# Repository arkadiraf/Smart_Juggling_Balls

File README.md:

# Smart Juggling Balls
Smart Juggling Balls is a project of mine which consists of 3 basic modules: 
arduino pro mini (compatible) MPU 6050 and nrf24
and a bunch of LEDS of course :)
The files I publish include the PCB manufacturing Gerber files
STL files for the casing (ment for 3d printing)
and some code I wrote.
The idea is to have colorful and happy juggling balls which can change lightning based on the sensor readings 
and remote maniputations communicating via nrf24.

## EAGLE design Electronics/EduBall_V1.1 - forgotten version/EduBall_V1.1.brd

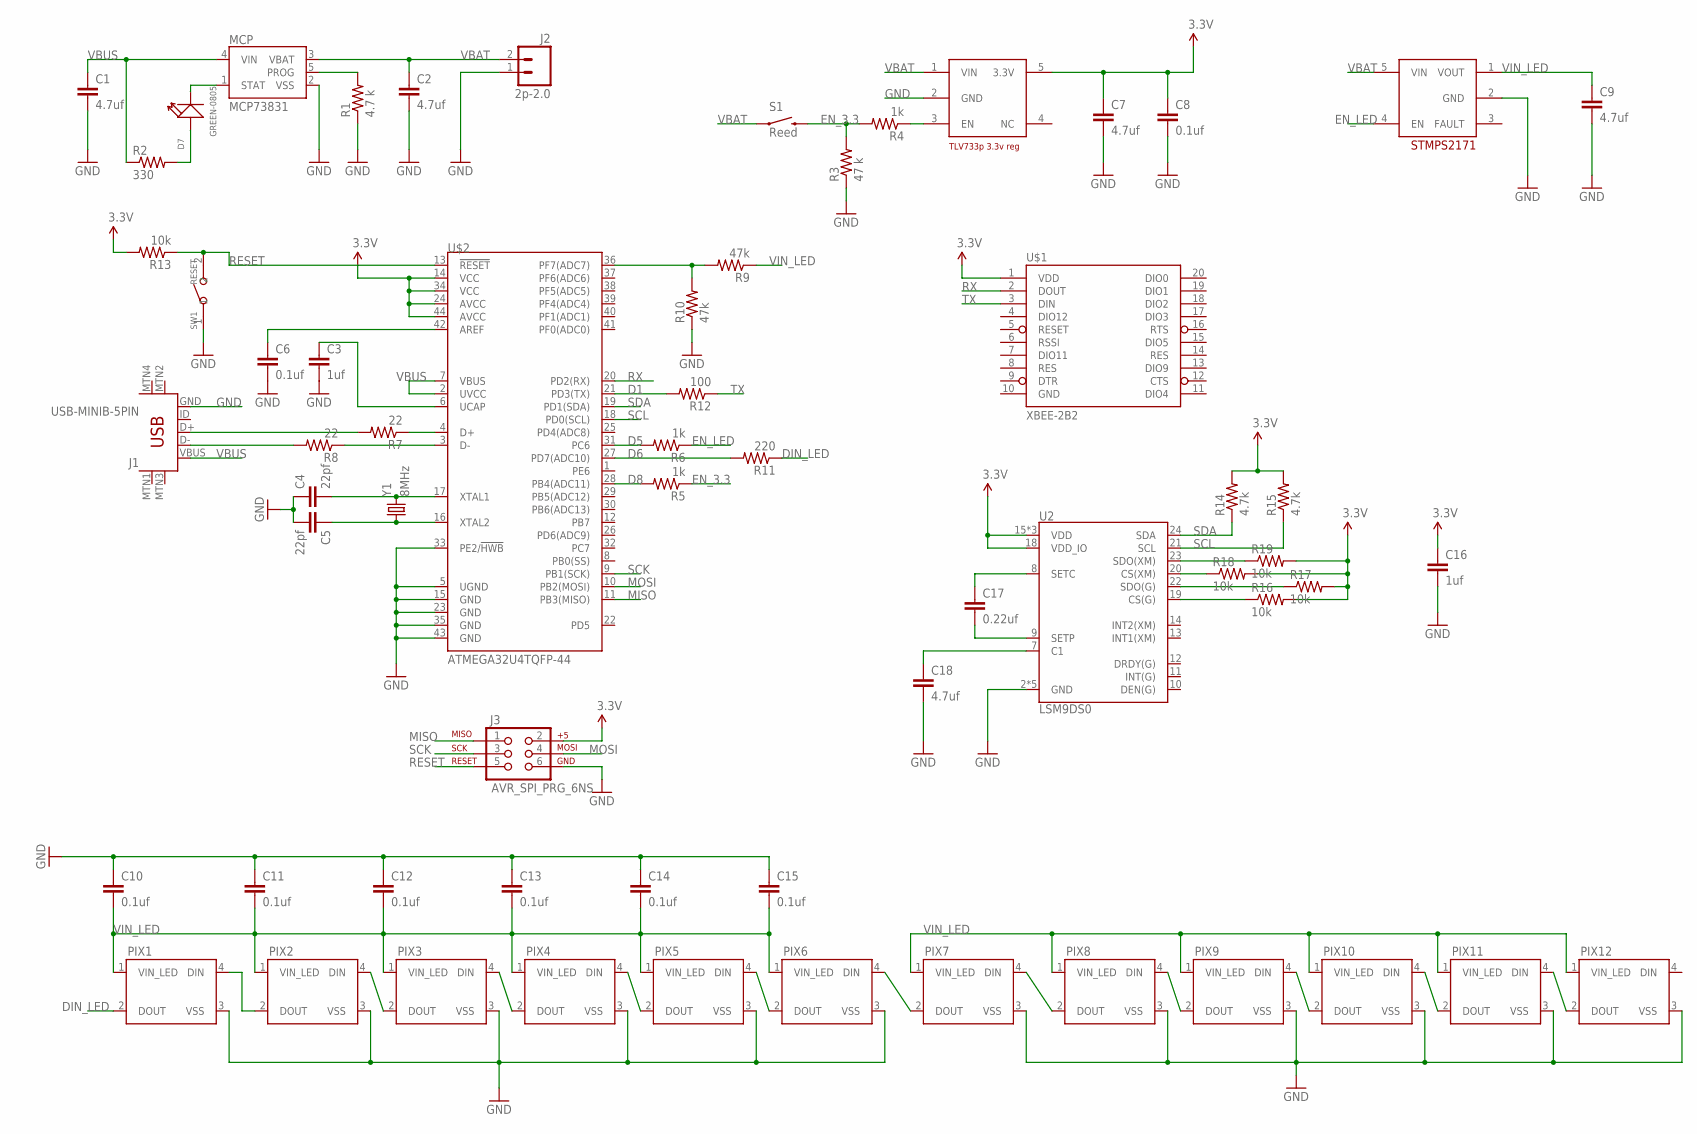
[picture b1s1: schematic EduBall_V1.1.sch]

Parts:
C1, C2, C7, C9, C18: 4.7uf; 0805
C3, C16: 1uf; 0805
C4, C5: 22pf; 0805
C6, C8, C10, C11, C12, C13, C14, C15: 0.1uf; 0805
C17: 0.22uf; 0805
D7: GREEN-0805; LED-0805
J1: USB-MINIB-5PIN; USB-MINIB
J2: 2p-2.0; JST-2-PTH-VERT
J3: AVR_SPI_PRG_6NS; 2X3-NS
MCP: MCP73831; SOT23-5
PIX1, PIX2, PIX3, PIX4, PIX5, PIX6, PIX7, PIX8, PIX9, PIX10, PIX11, PIX12: WS2812B
R1: 4.7 k; 0805
R2: 330; 0805
R3: 47 k; 0805
R4, R5, R6: 1k; 0805
R7, R8: 22; 0805
R9, R10: 47k; 0805
R11: 220; 0805
R12: 100; 0805
R13, R16, R17, R18, R19: 10k; 0805
R14, R15: 4.7k; 0805
S1: Reed; REED_SWITCH_PTH
STMP: STMPS2171; SOT23-5
SW1: RESET; SW2-2.6-3.0X2.5X1.2+0.4MM
TLV: TLV3333P; SOT23-5
U2: LSM9DS0; LGA-24
U$1: XBEE-2B2; XBEE-SILK
U$2: ATMEGA32U4TQFP-44; TQFP44
Y1: 8MHz; HC49US

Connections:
3.3V: C7.1, C8.1, C16.1, J3.2, R13.2, R14.2, R15.2, R16.2, R17.2, R18.2, R19.2, TLV.5 (3.3V), U2.15 (VDD), U2.16 (VDD), U2.17 (VDD), U2.18 (VDD_IO), U$1.1 (VDD), U$2.14 (VCC), U$2.24 (AVCC), U$2.34 (VCC), U$2.44 (AVCC)
D1: R12.2, U$2.21 (PD3(TX))
D5: R6.2, U$2.31 (PC6)
D6: R11.2, U$2.27 (PD7(ADC10))
D8: R5.2, U$2.28 (PB4(ADC11))
DIN_LED: PIX1.2 (DOUT), R11.1
EN_3.3: R3.2, R4.2, R5.1, S1.P$2 (2)
EN_LED: R6.1, STMP.4 (EN)
GND: C1.2, C2.2, C3.2, C4.1, C5.2, C6.2, C7.2, C8.2, C9.2, C10.1, C11.1, C12.1, C13.1, C14.1, C15.1, C16.2, C18.2, J1.GND, J2.1, J3.6, MCP.2 (VSS), PIX1.3 (VSS), PIX2.3 (VSS), PIX3.3 (VSS), PIX4.3 (VSS), PIX5.3 (VSS), PIX6.3 (VSS), PIX7.3 (VSS), PIX8.3 (VSS), PIX9.3 (VSS), PIX10.3 (VSS), PIX11.3 (VSS), PIX12.3 (VSS), R1.1, R3.1, R10.1, STMP.2 (GND), SW1.1, TLV.2 (GND), U2.2 (GND), U2.3 (GND), U2.4 (GND), U2.5 (GND), U2.6 (GND), U$1.10 (GND), U$2.5 (UGND), U$2.15 (GND), U$2.23 (GND), U$2.33 (PE2/!HWB), U$2.35 (GND), U$2.43 (GND)
MISO: J3.1, U$2.11 (PB3(MISO))
MOSI: J3.4, U$2.10 (PB2(MOSI))
unnamed: MCP.5 (PROG), R1.2
unnamed: PIX1.4 (DIN), PIX2.2 (DOUT)
unnamed: R4.1, TLV.3 (EN)
unnamed: D7.-, MCP.1 (STAT)
unnamed: D7.+, R2.2
unnamed: PIX2.4 (DIN), PIX3.2 (DOUT)
unnamed: PIX3.4 (DIN), PIX4.2 (DOUT)
unnamed: PIX4.4 (DIN), PIX5.2 (DOUT)
unnamed: PIX5.4 (DIN), PIX6.2 (DOUT)
unnamed: PIX6.4 (DIN), PIX7.2 (DOUT)
unnamed: PIX7.4 (DIN), PIX8.2 (DOUT)
unnamed: PIX8.4 (DIN), PIX9.2 (DOUT)
unnamed: PIX9.4 (DIN), PIX10.2 (DOUT)
unnamed: PIX10.4 (DIN), PIX11.2 (DOUT)
unnamed: PIX11.4 (DIN), PIX12.2 (DOUT)
unnamed: J1.D+, R7.2
unnamed: R7.1, U$2.4 (D+)
unnamed: R8.1, U$2.3 (D-)
unnamed: J1.D-, R8.2
unnamed: C3.1, U$2.6 (UCAP)
unnamed: C6.1, U$2.42 (AREF)
unnamed: C18.1, U2.7 (C1)
unnamed: C4.2, U$2.17 (XTAL1), Y1.2
unnamed: C5.1, U$2.16 (XTAL2), Y1.1
unnamed: R9.2, R10.2, U$2.36 (PF7(ADC7))
unnamed: C17.2, U2.9 (SETP)
unnamed: C17.1, U2.8 (SETC)
unnamed: R19.1, U2.23 (SDO(XM))
unnamed: R18.1, U2.20 (CS(XM))
unnamed: R17.1, U2.22 (SDO(G))
unnamed: R16.1, U2.19 (CS(G))
RESET: J3.5, R13.1, SW1.2, U$2.13 (!RESET)
RX: U$1.2 (DOUT), U$2.20 (PD2(RX))
SCK: J3.3, U$2.9 (PB1(SCK))
SCL: R15.1, U2.21 (SCL), U$2.18 (PD0(SCL))
SDA: R14.1, U2.24 (SDA), U$2.19 (PD1(SDA))
TX: R12.1, U$1.3 (DIN)
VBAT: C2.1, J2.2, MCP.3 (VBAT), S1.P$1 (1), STMP.5 (VIN), TLV.1 (VIN)
VBUS: C1.1, J1.VBUS, MCP.4 (VIN), R2.1, U$2.2 (UVCC), U$2.7 (VBUS)
VIN_LED: C9.1, C10.2, C11.2, C12.2, C13.2, C14.2, C15.2, PIX1.1 (VIN_LED), PIX2.1 (VIN_LED), PIX3.1 (VIN_LED), PIX4.1 (VIN_LED), PIX5.1 (VIN_LED), PIX6.1 (VIN_LED), PIX7.1 (VIN_LED), PIX8.1 (VIN_LED), PIX9.1 (VIN_LED), PIX10.1 (VIN_LED), PIX11.1 (VIN_LED), PIX12.1 (VIN_LED), R9.1, STMP.1 (VOUT)

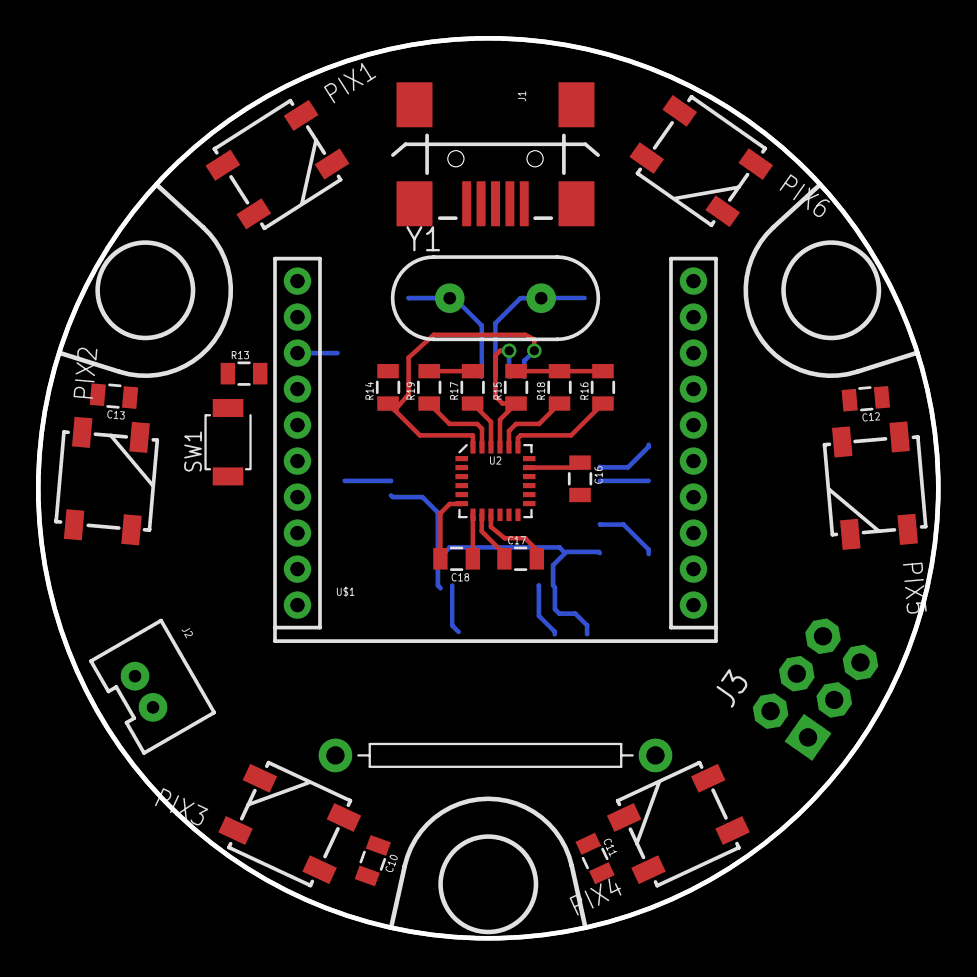
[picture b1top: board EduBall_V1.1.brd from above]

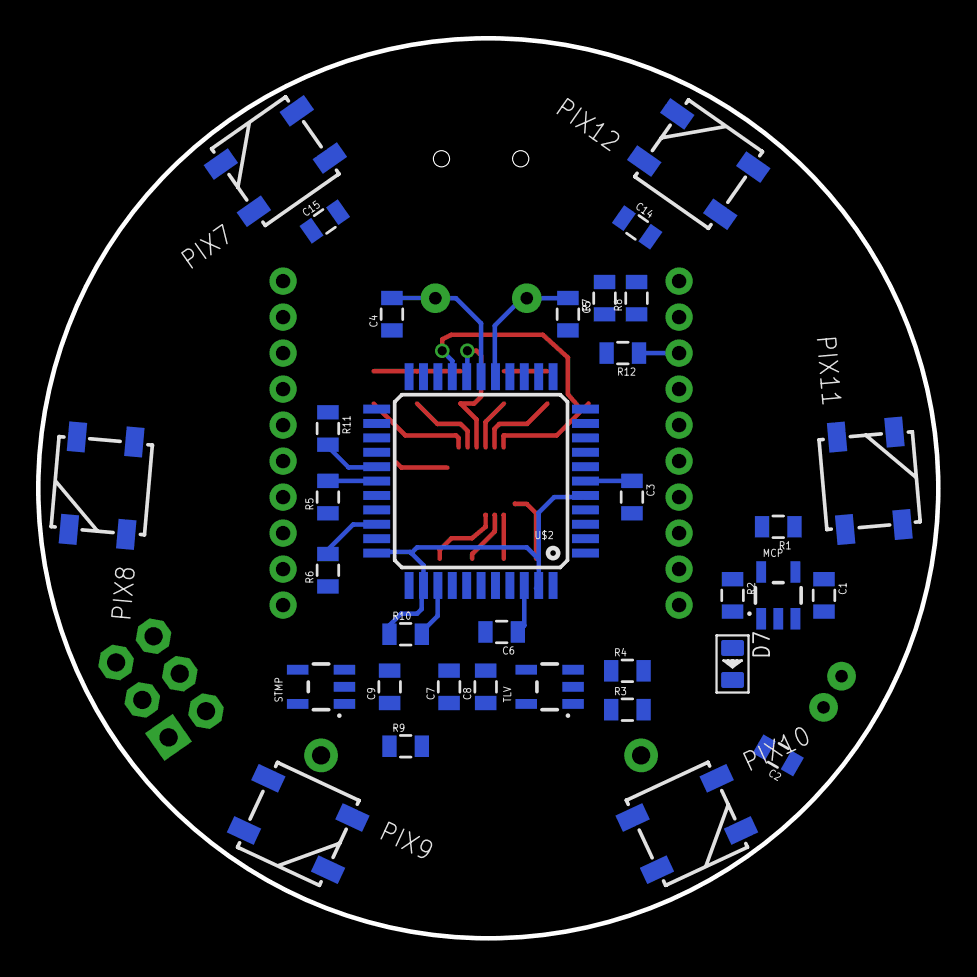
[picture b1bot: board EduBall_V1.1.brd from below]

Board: 2 copper layers, 50.0 x 50.0 mm, 62 parts (34 on the bottom side), 51 nets.

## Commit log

2021-02-03 Smart Juggling Commit

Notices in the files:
parts and their libraries:
SparkFun-Connectors: Licensing: Creative Commons ShareAlike 4.0 International - https://creativecommons.org/licenses/by-sa/4.0
